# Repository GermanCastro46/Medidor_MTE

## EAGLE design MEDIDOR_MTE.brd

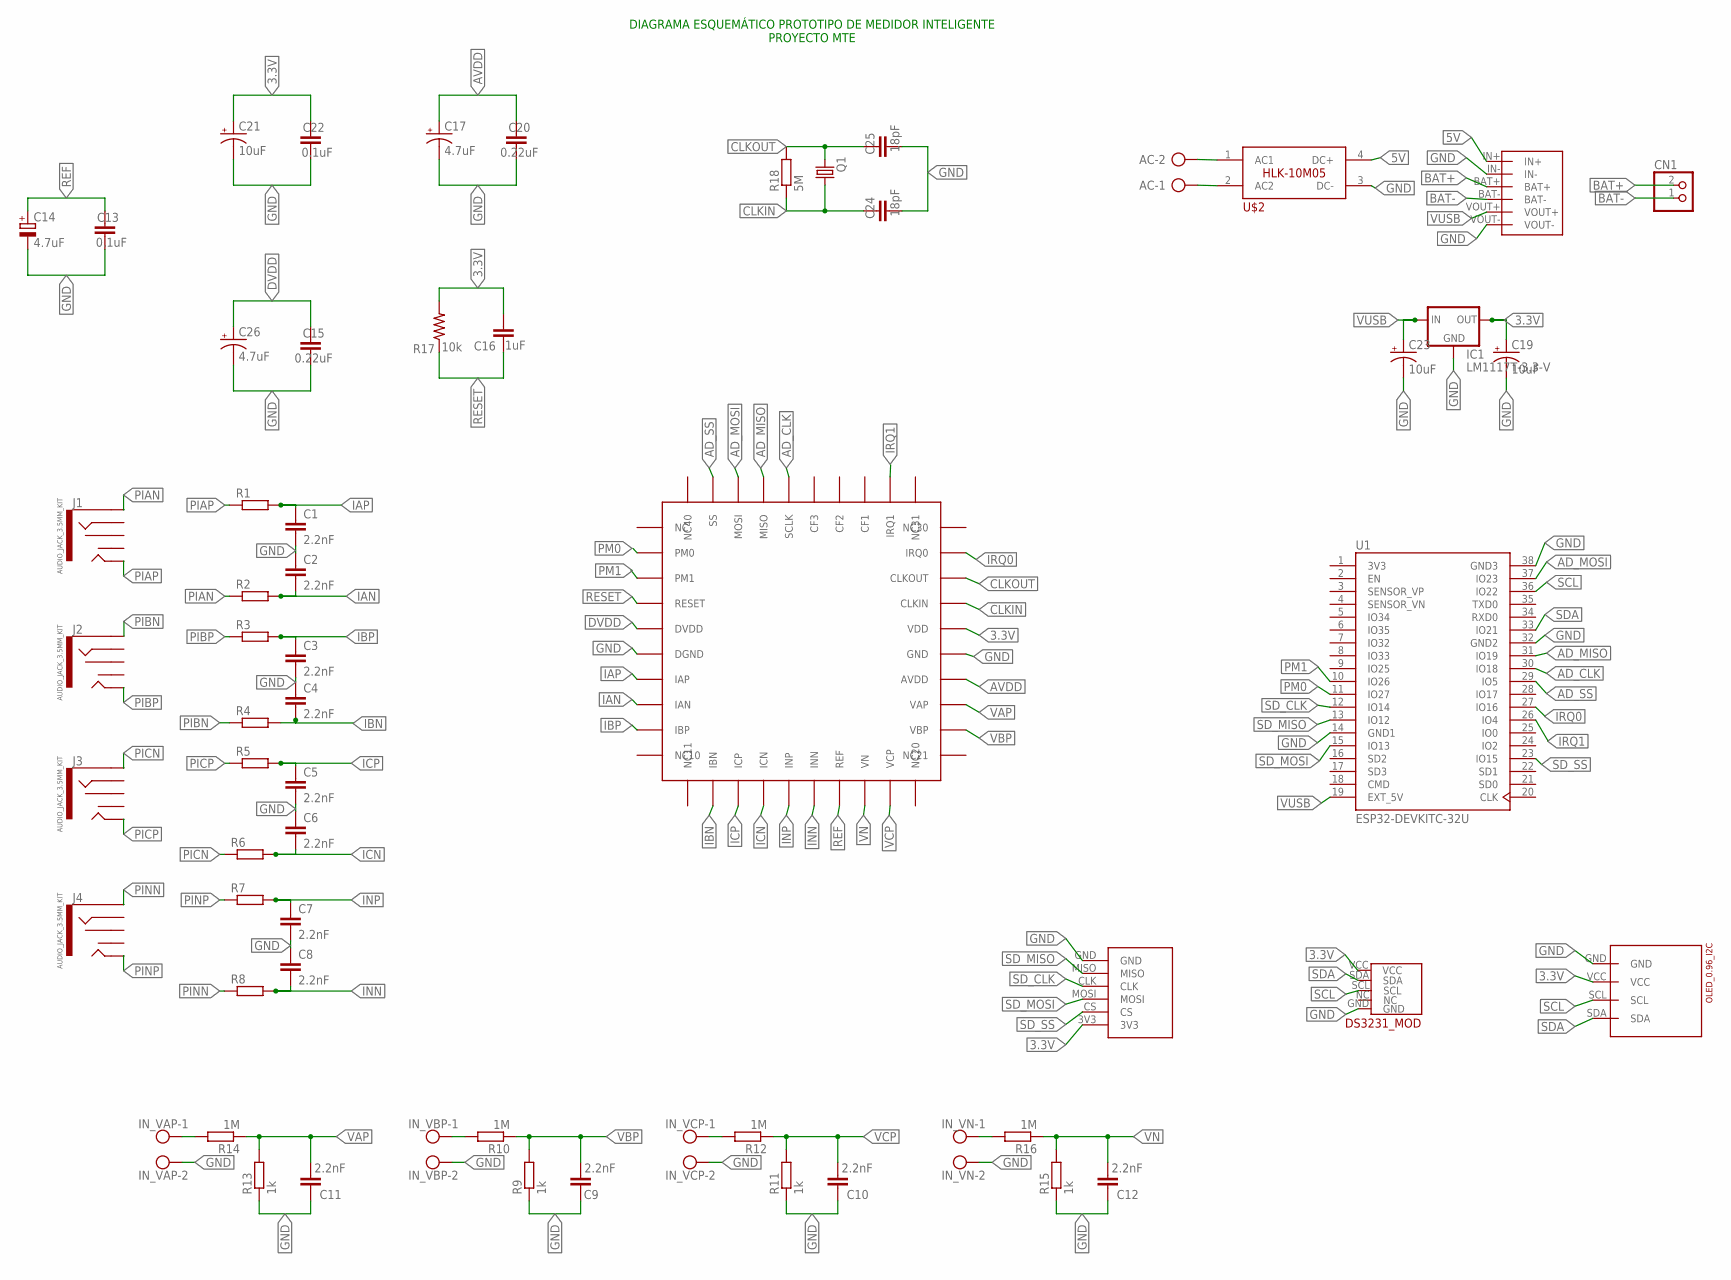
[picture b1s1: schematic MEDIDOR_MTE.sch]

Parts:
AC: AK500/2
C1, C2, C3, C4, C5, C6, C7, C8, C9, C10, C11, C12: 2.2nF; C025-025X050
C13, C22: 0.1uF; C025-025X050
C14, C17, C26: 4.7uF; E3,5-8
C15, C20: 0.22uF; C025-025X050
C16: 1uF; C025-025X050
C19, C23: 10uF; CPOL-RADIAL-2.5MM-5MM
C21: 10uF; E3,5-8
C24, C25: 18pF; C025-025X050
CN1: JST_2PIN-THM; JST-PH-2-THM
IC1: LM1117T-3.3-V; TO220V
IN_VAP: AK500/2
IN_VBP: AK500/2
IN_VCP: AK500/2
IN_VN: AK500/2
J1, J2, J3, J4: AUDIO_JACK_3.5MM_KIT; AUDIO-JACK-KIT
Q1: CRYSTALHC49S; HC49/S
R1, R2, R3, R4, R5, R6, R7, R8: R-EU_0207/12; 0207/12
R9, R11, R13, R15: 1k; 0207/12
R10, R12, R14, R16: 1M; 0207/12
R17: 10k; 0207/12
R18: 5M; 0207/12
U1: ESP32-DEVKITC-32U; MODULE_ESP32-DEVKITC-32U
U2: ADE7880; ADE7880_HDER
U$2: HLK-10M05
U$3: J5019_UPS
U$4: OLED_I2C_096; OLED_096_I2C
U$5: MODULO_MSD2; MICROSD-BREAKOUT
U$6: DS3231_MOD

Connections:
3.3V: C16.2, C19.1 (+), C21.+, C22.2, IC1.2 (OUT), R17.2, U2.PIN26 (VDD), U$4.VCC, U$5.3V3, U$6.VCC
3V3: U1.1 (3V3)
5V: U$2.4 (DC+), U$3.IN+
AD_CLK: U1.30 (IO18), U2.PIN36 (SCLK)
AD_MISO: U1.31 (IO19), U2.PIN37 (MISO)
AD_MOSI: U1.37 (IO23), U2.PIN38 (MOSI)
AD_SS: U1.29 (IO5), U2.PIN39 (SS)
AVDD: C17.+, C20.2, U2.PIN24 (AVDD)
BAT+: CN1.2 (1), U$3.BAT+
BAT-: CN1.1 (2), U$3.BAT-
CLKIN: C24.2, Q1.1, R18.1, U2.PIN27 (CLKIN)
CLKOUT: C25.2, Q1.2, R18.2, U2.PIN28 (CLKOUT)
DVDD: C15.2, C26.+, U2.PIN5 (DVDD)
GND: C1.2, C2.1, C3.2, C4.1, C5.2, C6.1, C7.2, C8.1, C9.1, C10.1, C11.1, C12.1, C13.1, C14.-, C15.1, C17.-, C19.2 (-), C20.1, C21.-, C22.1, C23.2 (-), C24.1, C25.1, C26.-, IC1.1 (GND), IN_VAP.2, IN_VBP.2, IN_VCP.2, IN_VN.2, R9.1, R11.1, R13.1, R15.1, U1.14 (GND1), U1.32 (GND2), U1.38 (GND3), U2.PIN6 (DGND), U2.PIN25 (GND), U$2.3 (DC-), U$3.IN-, U$3.VOUT-, U$4.GND, U$5.GND, U$6.GND
IAN: C2.2, R2.2, U2.PIN8 (IAN)
IAP: C1.1, R1.2, U2.PIN7 (IAP)
IBN: C4.2, R4.2, U2.PIN12 (IBN)
IBP: C3.1, R3.2, U2.PIN9 (IBP)
ICN: C6.2, R6.2, U2.PIN14 (ICN)
ICP: C5.1, R5.2, U2.PIN13 (ICP)
INN: C8.2, R8.2, U2.PIN16 (INN)
INP: C7.1, R7.2, U2.PIN15 (INP)
IRQ0: U1.27 (IO16), U2.PIN29 (IRQ0)
IRQ1: U1.26 (IO4), U2.PIN32 (IRQ1)
unnamed: IN_VBP.1, R10.2
unnamed: IN_VCP.1, R12.2
unnamed: IN_VAP.1, R14.2
unnamed: IN_VN.1, R16.2
unnamed: AC.2, U$2.1 (AC1)
unnamed: AC.1, U$2.2 (AC2)
PIAN: J1.SLEEVE, R2.1
PIAP: J1.TIP, R1.1
PIBN: J2.SLEEVE, R4.1
PIBP: J2.TIP, R3.1
PICN: J3.SLEEVE, R6.1
PICP: J3.TIP, R5.1
PINN: J4.SLEEVE, R8.1
PINP: J4.TIP, R7.1
PM0: U1.11 (IO27), U2.PIN2 (PM0)
PM1: U1.10 (IO26), U2.PIN3 (PM1)
REF: C13.2, C14.+, U2.PIN17 (REF)
RESET: C16.1, R17.1, U2.PIN4 (RESET)
SCL: U1.36 (IO22), U$4.SCL, U$6.SCL
SDA: U1.33 (IO21), U$4.SDA, U$6.SDA
SD_CLK: U1.12 (IO14), U$5.CLK
SD_MISO: U1.13 (IO12), U$5.MISO
SD_MOSI: U1.15 (IO13), U$5.MOSI
SD_SS: U1.23 (IO15), U$5.CS
VAP: C11.2, R13.2, R14.1, U2.PIN23 (VAP)
VBP: C9.2, R9.2, R10.1, U2.PIN22 (VBP)
VCP: C10.2, R11.2, R12.1, U2.PIN19 (VCP)
VN: C12.2, R15.2, R16.1, U2.PIN18 (VN)
VUSB: C23.1 (+), IC1.3 (IN), U1.19 (EXT_5V), U$3.VOUT+

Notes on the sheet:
DIAGRAMA ESQUEMÁTICO PROTOTIPO DE MEDIDOR INTELIGENTE PROYECTO MTE

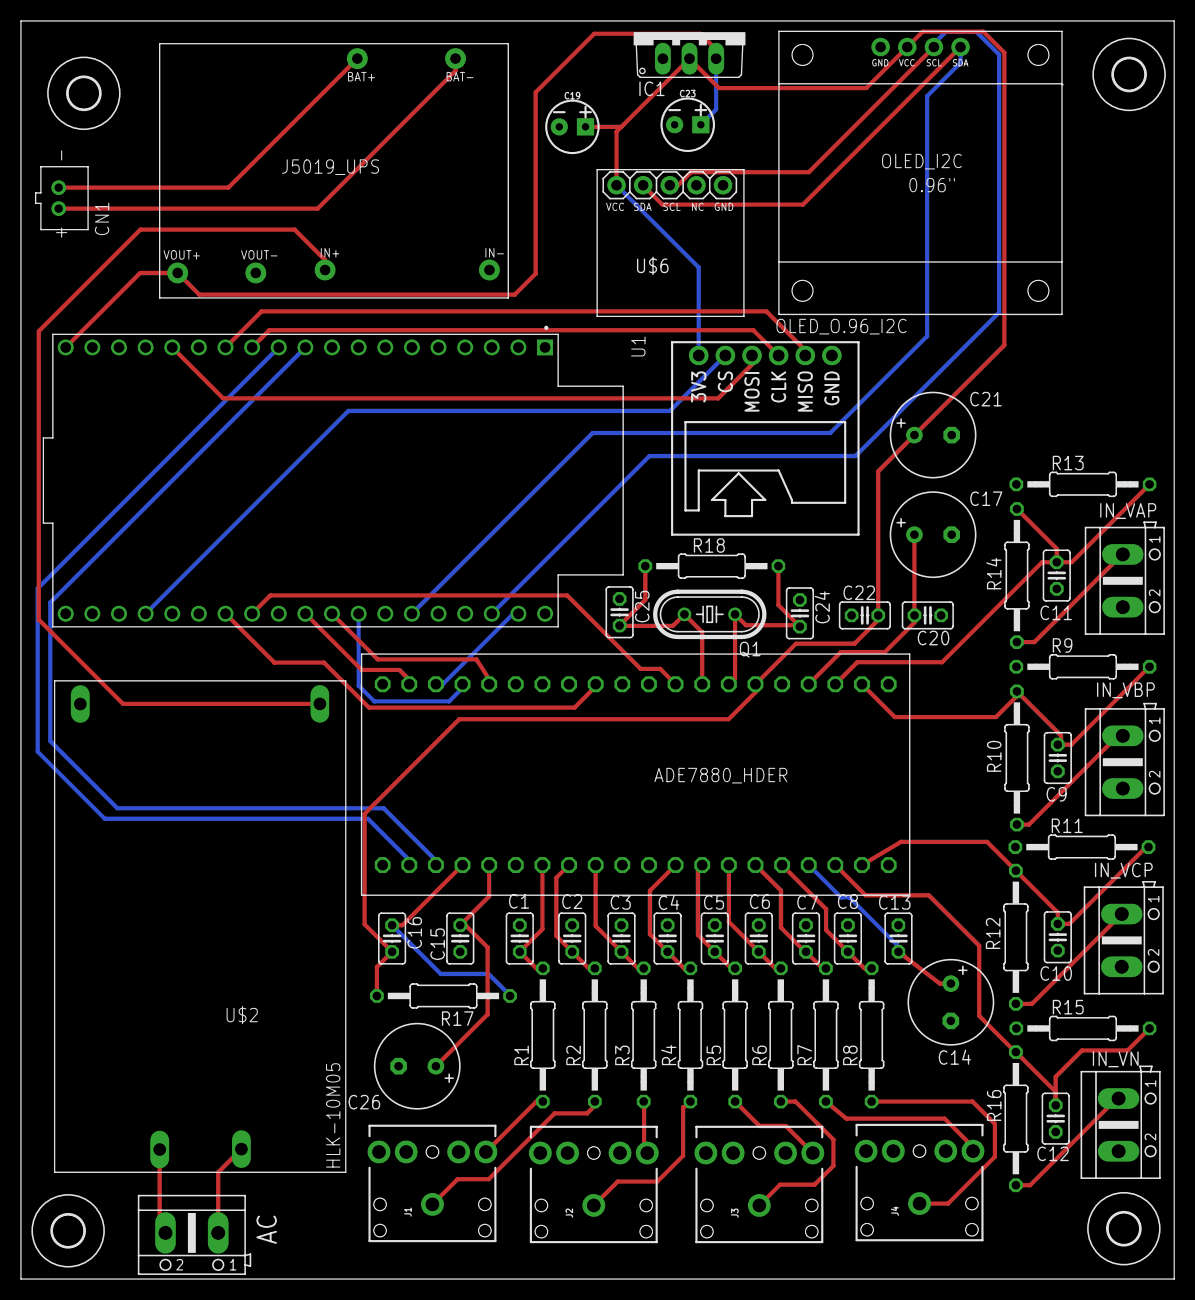
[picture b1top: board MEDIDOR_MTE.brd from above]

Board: 2 copper layers, 110.0 x 120.0 mm, 66 parts (0 on the bottom side), 52 nets.

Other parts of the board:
U$7, U$8, U$9, U$10: 3,0

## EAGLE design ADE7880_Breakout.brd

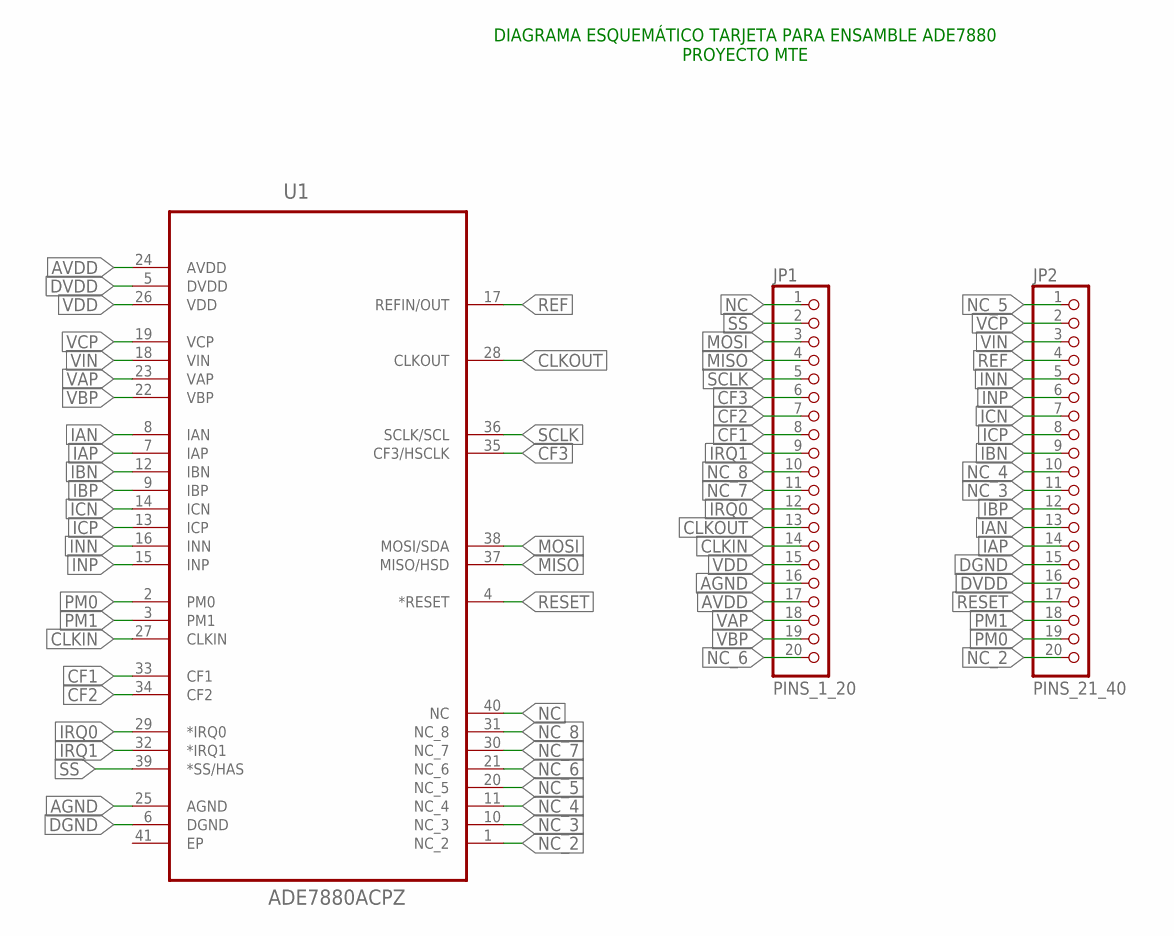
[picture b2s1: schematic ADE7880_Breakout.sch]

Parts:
JP1: PINS_1_20; 1X20
JP2: PINS_21_40; 1X20
U1: ADE7880ACPZ; QFN50P600X600X80-41N

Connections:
AGND: JP1.16, U1.25 (AGND)
AVDD: JP1.17, U1.24 (AVDD)
CF1: JP1.8, U1.33 (CF1)
CF2: JP1.7, U1.34 (CF2)
CF3: JP1.6, U1.35 (CF3/HSCLK)
CLKIN: JP1.14, U1.27 (CLKIN)
CLKOUT: JP1.13, U1.28 (CLKOUT)
DGND: JP2.15, U1.6 (DGND)
DVDD: JP2.16, U1.5 (DVDD)
IAN: JP2.13, U1.8 (IAN)
IAP: JP2.14, U1.7 (IAP)
IBN: JP2.9, U1.12 (IBN)
IBP: JP2.12, U1.9 (IBP)
ICN: JP2.7, U1.14 (ICN)
ICP: JP2.8, U1.13 (ICP)
INN: JP2.5, U1.16 (INN)
INP: JP2.6, U1.15 (INP)
IRQ0: JP1.12, U1.29 (*IRQ0)
IRQ1: JP1.9, U1.32 (*IRQ1)
MISO: JP1.4, U1.37 (MISO/HSD)
MOSI: JP1.3, U1.38 (MOSI/SDA)
NC: JP1.1, U1.40 (NC)
NC_2: JP2.20, U1.1 (NC_2)
NC_3: JP2.11, U1.10 (NC_3)
NC_4: JP2.10, U1.11 (NC_4)
NC_5: JP2.1, U1.20 (NC_5)
NC_6: JP1.20, U1.21 (NC_6)
NC_7: JP1.11, U1.30 (NC_7)
NC_8: JP1.10, U1.31 (NC_8)
PM0: JP2.19, U1.2 (PM0)
PM1: JP2.18, U1.3 (PM1)
REF: JP2.4, U1.17 (REFIN/OUT)
RESET: JP2.17, U1.4 (*RESET)
SCLK: JP1.5, U1.36 (SCLK/SCL)
SS: JP1.2, U1.39 (*SS/HAS)
VAP: JP1.18, U1.23 (VAP)
VBP: JP1.19, U1.22 (VBP)
VCP: JP2.2, U1.19 (VCP)
VDD: JP1.15, U1.26 (VDD)
VIN: JP2.3, U1.18 (VIN)

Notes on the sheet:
DIAGRAMA ESQUEMÁTICO TARJETA PARA ENSAMBLE ADE7880 PROYECTO MTE

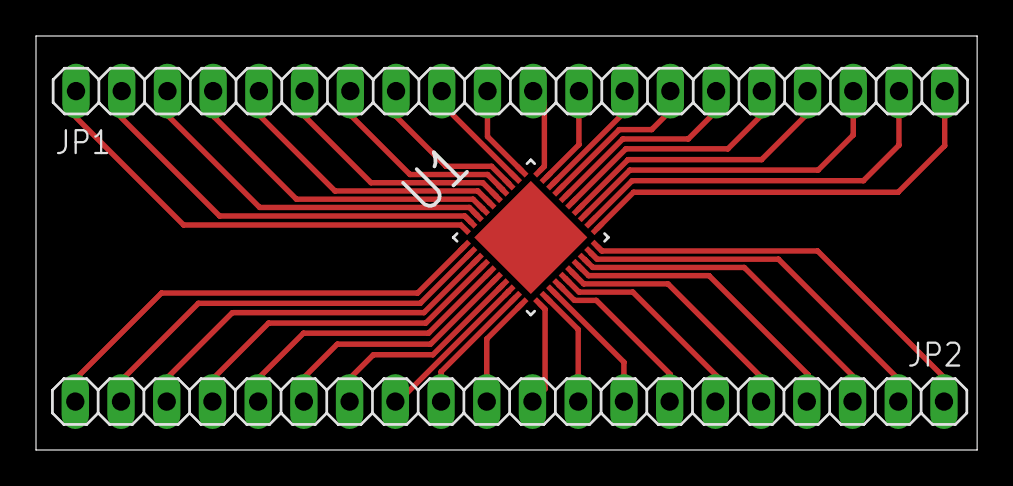
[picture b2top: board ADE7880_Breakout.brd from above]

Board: 2 copper layers, 52.3 x 23.0 mm, 3 parts (0 on the bottom side), 40 nets.

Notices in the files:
parts and their libraries:
SparkFun-Connectors: Licensing: Creative Commons ShareAlike 4.0 International - https://creativecommons.org/licenses/by-sa/4.0
